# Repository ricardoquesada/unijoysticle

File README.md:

# The UniJoystiCle

The UniJoystiCle, the ultimate unicycle simulator.

It allows you to play Commodore 64 [unicycle video games](https://github.com/ricardoquesada/c64-the-uni-games) with real unicycles. Unique immersive experience, much better than VR.

This repository contains:

* the [schematic + PCB board](https://github.com/ricardoquesada/unijoysticle/tree/master/schematic) to build your own Wi-Fi receiver
* the [firmware](https://github.com/ricardoquesada/unijoysticle/tree/master/esp8266_firmware) that runs on the Wi-Fi receiver
* the [iOS client](https://github.com/ricardoquesada/unijoysticle/tree/master/client_ios) / [Android client](https://github.com/ricardoquesada/unijoysticle/tree/master/client_android) / [Desktop client](https://github.com/ricardoquesada/unijoysticle/tree/master/client_desktop): they send the packets to the Wi-Fi receiver

## Further info

* [Documentation](DOCUMENTATION.md)
* [Home page](http://retro.moe/unijoysticle)

## Videos

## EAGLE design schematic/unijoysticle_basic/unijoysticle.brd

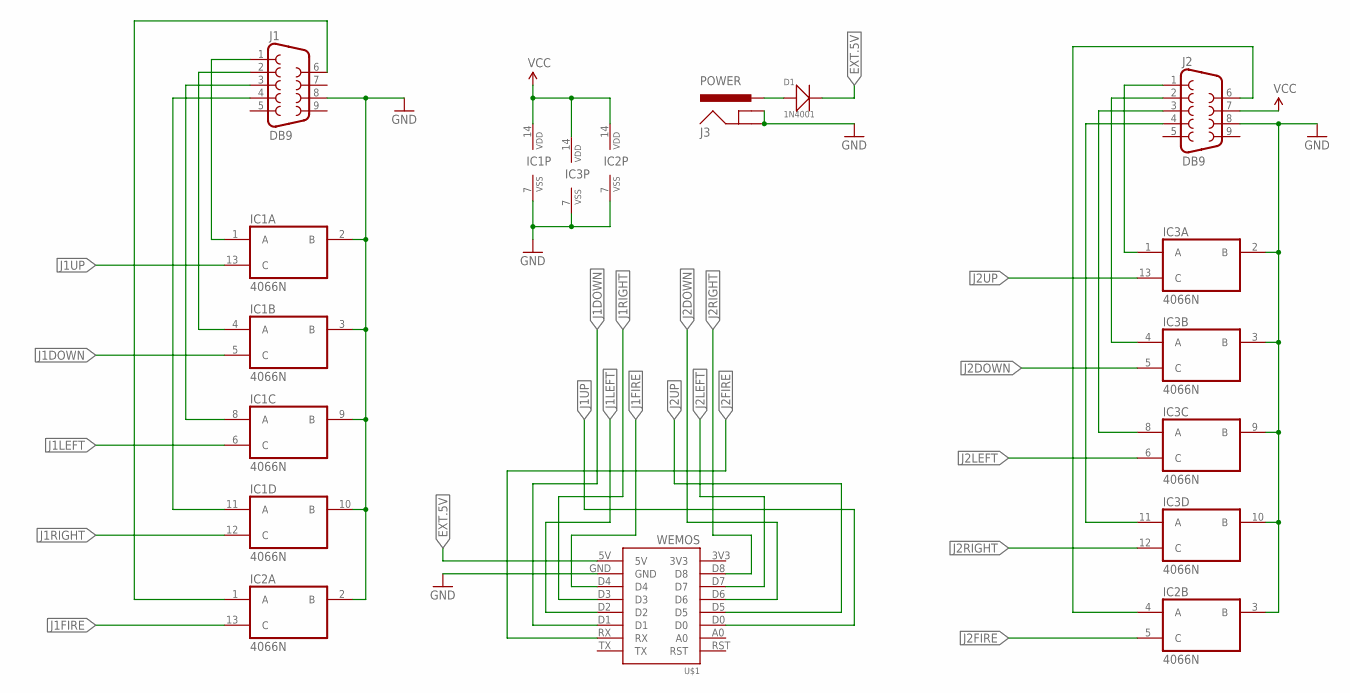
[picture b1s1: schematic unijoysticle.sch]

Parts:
D1: 1N4001; DO-41
IC1, IC2, IC3: 4066N; DIL14; MPN SN74HC4066N
J1, J2: DB9; MPN 618009231121
J3: POWER; POWER_JACK_SLOT
U$1: WEMOS

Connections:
EXT.5V: D1.2 (-), U$1.5V
GND: IC1.2 (B), IC1.3 (B), IC1.7 (VSS), IC1.9 (B), IC1.10 (B), IC2.2 (B), IC2.3 (B), IC2.7 (VSS), IC3.2 (B), IC3.3 (B), IC3.7 (VSS), IC3.9 (B), IC3.10 (B), J1.8, J2.8, J3.GND@1 (GNDBREAK), J3.GND@2 (GND), U$1.GND
J1DOWN: IC1.5 (C), U$1.D1
J1FIRE: IC2.13 (C), U$1.D4
J1LEFT: IC1.6 (C), U$1.D2
J1RIGHT: IC1.12 (C), U$1.D3
J1UP: IC1.13 (C), U$1.D0
J2DOWN: IC3.5 (C), U$1.D6
J2FIRE: IC2.5 (C), U$1.RX
J2LEFT: IC3.6 (C), U$1.D7
J2RIGHT: IC3.12 (C), U$1.D8
J2UP: IC3.13 (C), U$1.D5
unnamed: D1.1 (+), J3.PWR
unnamed: IC1.1 (A), J1.1
unnamed: IC1.4 (A), J1.2
unnamed: IC1.8 (A), J1.3
unnamed: IC1.11 (A), J1.4
unnamed: IC3.1 (A), J2.1
unnamed: IC3.4 (A), J2.2
unnamed: IC3.8 (A), J2.3
unnamed: IC3.11 (A), J2.4
unnamed: IC2.1 (A), J1.6
unnamed: IC2.4 (A), J2.6
VCC: IC1.14 (VDD), IC2.14 (VDD), IC3.14 (VDD), J2.7

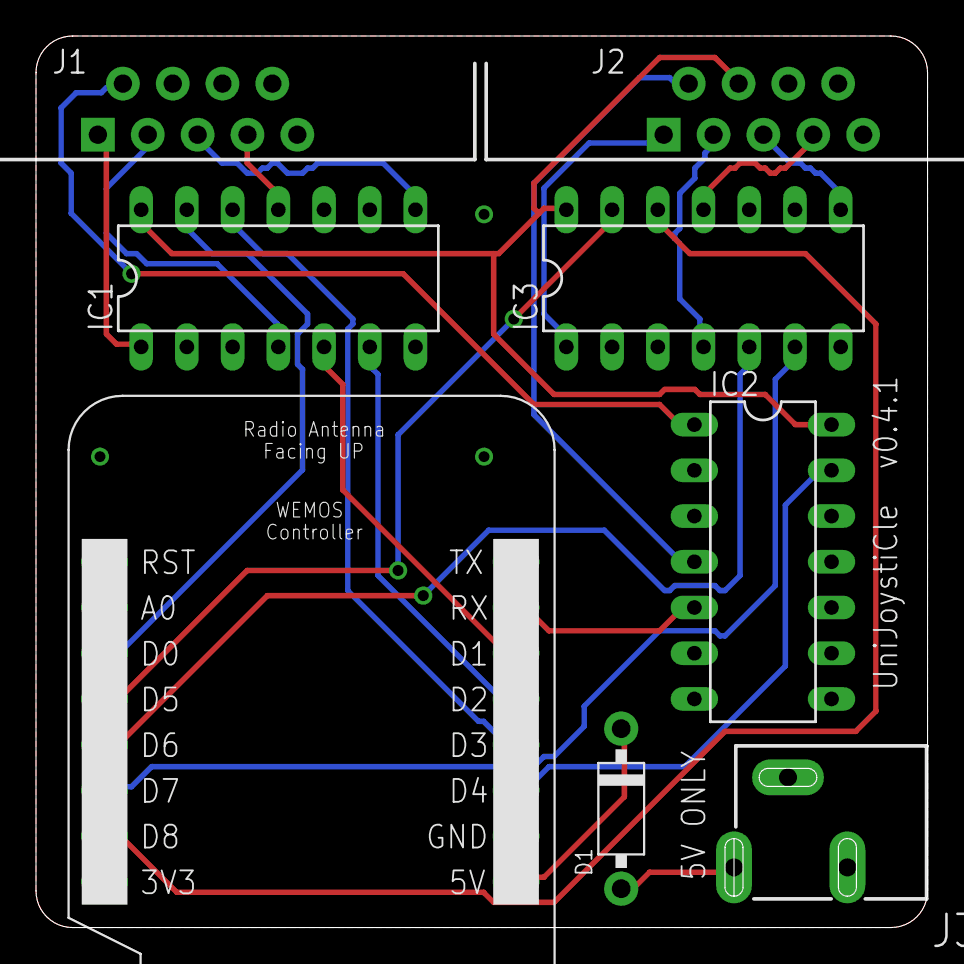
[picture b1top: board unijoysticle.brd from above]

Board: 2 copper layers, 49.5 x 49.5 mm, 8 parts (0 on the bottom side), 24 nets.

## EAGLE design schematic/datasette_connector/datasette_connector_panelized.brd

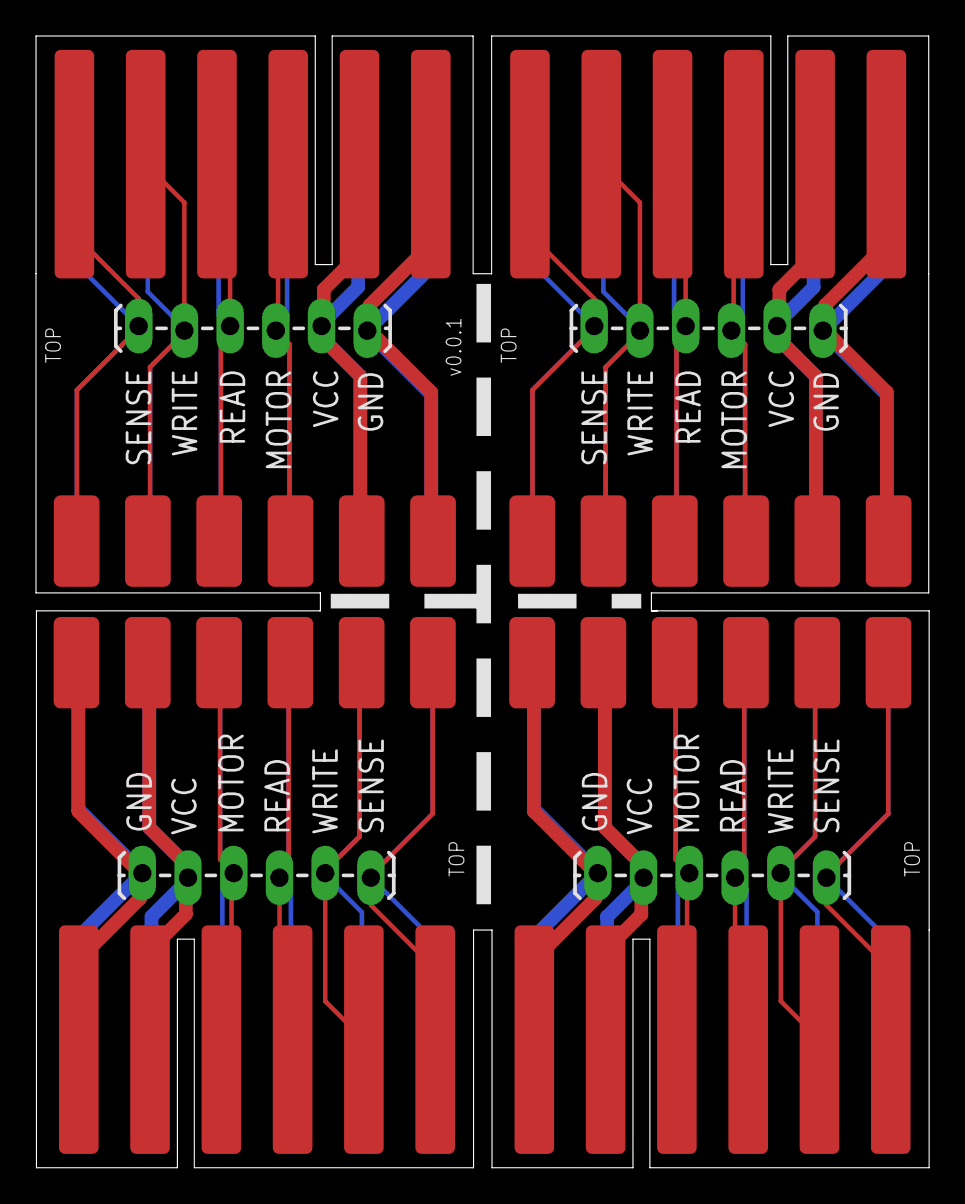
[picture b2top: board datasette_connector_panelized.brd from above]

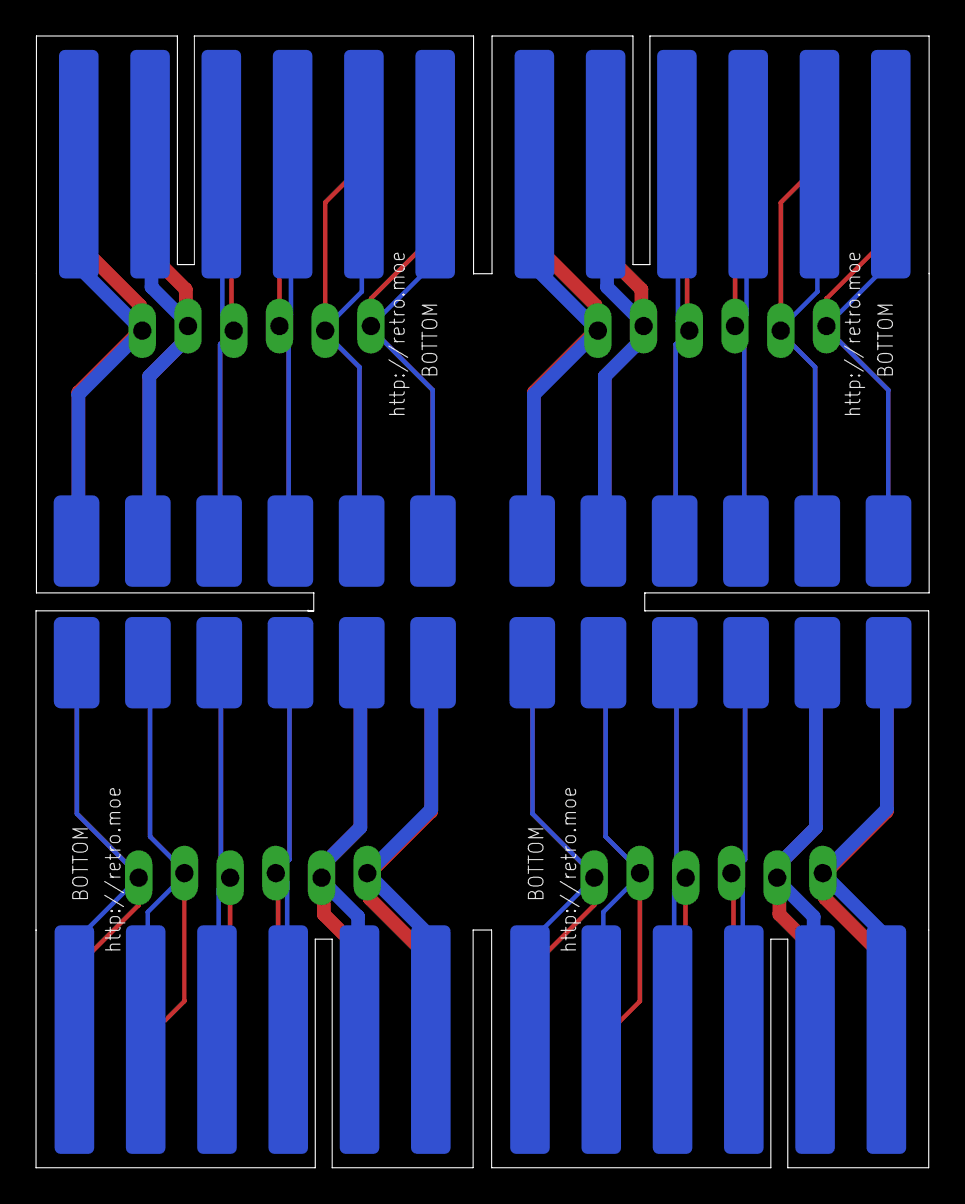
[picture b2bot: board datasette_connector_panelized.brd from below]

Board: 2 copper layers, 49.6 x 62.9 mm, 12 parts (4 on the bottom side), 24 nets.

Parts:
CN1, CN11, CN12, CN13: C64_CASETTE_EDGE; C64_CASSETTE
CN3, CN31, CN32, CN33: C64_CASETTE_CONN; C64_CASSETTE_CONN
JP, JP1, JP2, JP3: C64 CON; 1X06_LOCK_LONGPADS

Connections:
GND: CN1.1, CN1.A, CN3.1, CN3.A, JP.1
GND1: CN11.1, CN11.A, CN31.1, CN31.A, JP1.1
GND2: CN12.1, CN12.A, CN32.1, CN32.A, JP2.1
GND3: CN13.1, CN13.A, CN33.1, CN33.A, JP3.1
unnamed: CN1.5, CN1.E, CN3.5, CN3.E, JP.5
unnamed: CN1.6, CN1.F, CN3.6, CN3.F, JP.6
unnamed: CN1.3, CN1.C, CN3.3, CN3.C, JP.3
unnamed: CN11.5, CN11.E, CN31.5, CN31.E, JP1.5
unnamed: CN12.5, CN12.E, CN32.5, CN32.E, JP2.5
unnamed: CN13.5, CN13.E, CN33.5, CN33.E, JP3.5
unnamed: CN1.4, CN1.D, CN3.4, CN3.D, JP.4
unnamed: CN11.6, CN11.F, CN31.6, CN31.F, JP1.6
unnamed: CN12.6, CN12.F, CN32.6, CN32.F, JP2.6
unnamed: CN13.6, CN13.F, CN33.6, CN33.F, JP3.6
unnamed: CN11.3, CN11.C, CN31.3, CN31.C, JP1.3
unnamed: CN12.3, CN12.C, CN32.3, CN32.C, JP2.3
unnamed: CN13.3, CN13.C, CN33.3, CN33.C, JP3.3
unnamed: CN11.4, CN11.D, CN31.4, CN31.D, JP1.4
unnamed: CN12.4, CN12.D, CN32.4, CN32.D, JP2.4
unnamed: CN13.4, CN13.D, CN33.4, CN33.D, JP3.4
VCC: CN1.2, CN1.B, CN3.2, CN3.B, JP.2
VCC1: CN11.2, CN11.B, CN31.2, CN31.B, JP1.2
VCC2: CN12.2, CN12.B, CN32.2, CN32.B, JP2.2
VCC3: CN13.2, CN13.B, CN33.2, CN33.B, JP3.2

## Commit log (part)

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2016-09-02 android client: fire works as expected on dpad
2016-09-02 android client: dpad mode draws arrows WIP
2016-09-03 android client: radio dpad checked by default
2016-09-03 fix: android client. preferences are read from activites
2016-09-04 android client: server pref summary is updated onChanges
2016-09-04 android client: store images
2016-09-04 android client: resubmitted
    id is: moe.retro.unijosyticle (one unijosyticle)
    floating button: goes to documentation
    using correct title bar in actionbar
    doesn't show status bar
2016-09-04 docs: android badge size
2016-09-04 docs: android badge
2016-09-06 android client: preferences working!
2016-09-06 android client: removed unused strings
2016-09-06 android client: incorrect default for movement
2016-09-06 android client: version is 0.3
2016-09-06 docs: updates changelog
2016-09-06 docs: updates README
2016-09-07 docs: added another bug to Bugs
2016-09-08 docs: updated documentation
2016-09-08 docs: more trobleshooting info
2016-09-09 feat: Commando Mode
    Control both joysticks with one game controller
    It is called Commando Mode because you can play an unmodified
    Commando game and fire with Button A, and thorw granedes with
    Button B!!
2016-09-10 feat: Commando mode for Android
2016-09-10 fix: android client: version is 0.4
2016-09-10 fix: android client: disable radio when Commando
2016-09-10 ios client: fixes in Commando mode
    remove obsolte screenshots. using only 5.5" screenshots now
2016-09-12 docs: more info about the Commando mode
2016-09-12 docs: updated screenshots in doc
2016-09-12 docs: add game controller image
2016-09-12 docs: updated info about android controllers
2016-09-13 docs: note about WiFi Direct game controllers
2016-09-13 ios/android client: send state twice per change
    and not 60 times per second. saves battery life!
    Also fixes joystick movements in android.
2016-09-13 android client: update exclude dirs
2016-09-13 ios client: fix. remove optionals from non-optional nodes
2016-09-14 board: missing via and better labels
2016-09-14 android client: oops, dpad mode working again
2016-09-14 docs: improved doc
2016-09-14 docs: correct width/height
2016-09-14 docs: typos
2016-09-16 ios client: fix: improves iCade support
    Buttons A and D are Fire (not only A)
    Buttons B and C are Jump (not only B)
2016-09-16 ios client: verison 0.4.3
2016-09-17 android client: add analytics
    to see what is the most popular mode
2016-09-17 android client: restore SeekBarPreference
2016-09-17 android client: more cleanups
2016-09-19 client android / firmware: fixes
    client android: display error dialog if can't resolve server name
    firmware: added code for WPS support. disabled by default
2016-09-19 android client: OK instead of Ok
2016-09-19 firmware: feat: store WPS credentials in EEPROM
2016-09-20 firmware: fix: no compile-time options
    everything can be changed in runtime by setting certain values
    in the EEPROM. No possible yet to change those values, but
    will be enabled soon via TCP
2016-09-20 firmware: feat: from the webserver everything can be set
2016-09-20 firmware: better settings
2016-09-20 firmware: using C++ literals for html page
2016-09-20 docs: fixes about the barrel jack
2016-09-20 firmware: shows SSID in webpage
2016-09-20 docs: bugs are reported in the issue tracker
2016-09-21 firmware: reset joy stats + more bug fixes
2016-09-21 firmware: bette webpage
2016-09-21 firmware: redirect works ok
2016-09-22 android client: adds missing text strings for in18
2016-09-22 android client: resolves unijoysticle.local + unijosyticle mode
    unijoysticle mode:
    - correct rotation: uses x instead of y
    - z > threshold instead of z < -threshold
2016-09-22 docs: changelog
2016-09-22 android client: report error if cannot resolve server address
2016-09-22 android client: analyzer fixes
2016-09-22 android client: NSD major fix
    resolves correctly. does not try to send another rquest
    is one is still in progress
2016-09-23 ios client: migrated to Xcode 8 + swift 2.3
2016-09-23 ios client: adds Stats & SEttings for WiFi device
2016-09-23 android client: Server -> WiFi device
2016-09-23 ios controller: shows version in settings
    and other minor fixes
2016-09-23 docs: documentation improved
2016-09-23 docs: adds TM
2016-09-24 android client: correct name
2016-09-24 firmware: test for web update
2016-09-24 Create gh-pages branch via GitHub
2016-09-24 docs: test
2016-09-24 firmware
2016-09-24 firmware latest version
2016-09-24 firmware: upgrade firmware works
2016-09-24 new firmware
2016-09-24 firmware: fetch firmware from correct localtion
2016-09-24 firmware: correct URL for upgrade
2016-09-24 latest firmware
2016-09-24 more info
2016-09-24 docs: info about install firmware
2016-09-25 firmware v0.4.3
2016-09-25 icons
2016-09-25 fixes in icons
2016-09-25 docs: more info about flashing the nodemcu
2016-09-25 docs: more on flashing firmware
2016-09-30 ios client: remove ?)! ... just a ! is enough
2016-10-03 docs: better power consumtion
2016-10-07 schematic: adds diode again
    I don't know if it is really needed, but it is scary
    to see the c64 LED on, even if the computer is off
    when the unijosyticle is being powered by USB,
    but externally connected to the datassette port
2016-10-07 board: adds 3 vias
2016-10-07 board: label "unijoysticle" better position
2016-10-07 board: longer pads for wemos
2016-10-14 desktop client: displays the arrows
    still WIP
2016-10-14 desktop client. getting better
2016-10-14 deskop client: adding icons and other stuff
2016-10-16 desktop client: utils and other files
2016-10-18 desktop client: resolves mdns
    and sends joystate
2016-10-18 desktop client: adds quit
2016-10-19 desktop client: better handling the creation...
    ...of Main Window
2016-10-19 desktop client: linear mode fixes
    no more settings. added possibility to change both
    joysticks with two different sliders
2016-10-19 desktop client: adds preferences
2016-10-19 desktop client: better internal design...
    ... in settings.
    settings are monolithic now. easier. don't need the super-dooper
    modular design
2016-10-20 desktop client: command mode works
    ...but no gamepad support yet
2016-10-25 desktop client: initial gamepad support
2016-10-28 Linear -> Commodore Home
2016-10-29 android client: clear event after 160ms in Home mode
2016-10-30 android client: home fixes
    alarm switch works
    fix play/stop buttons
2016-11-04 ios client: Commodore Home almost there
2016-11-04 ios client: migrated to Swift v3.0
2016-11-05 desktop client: commodore home
2016-11-07 desktop client: works with dpads. all modes
2016-11-07 desktop client: fixes crashes
2016-11-07 docs: changelog update for buttons X and Y in Commando mode
2016-11-07 firmware: allows changing the MDNS name
    v0.4.4
2016-11-07 firmware: Name, not name
2016-11-07 desktoip client: better defaults for mdi widget
2016-11-07 desktoip client: correct name for mac
2016-11-07 latest firmware is v0.4.4
2016-11-07 adds windows app
2016-11-07 downloads links
2016-11-07 better homepage
2016-11-08 display version correctly
2016-11-08 binary for Mac is v0.4.0
2016-11-08 no longer beta
2016-11-08 spaces in name
2016-11-08 documentation updates
2016-11-08 firmare v0.4.5
2016-11-08 firmware: remove reset
2016-11-08 docs: screenshots for documentation
2016-11-08 docs: new screnshot with commodore home
2016-11-08 docs: changelog fixes
2016-11-11 schematic: datasette port bottom names fix
2016-11-12 board: datasette: adds panelized version
2016-11-14 laytout: datasette connect panelized fixes
    gap has 1mm instead of 0.6mm since Seeed Studio doesn't support it
2016-11-14 v0.4.1 for macOS
2016-11-14 v04.1. for windows client
2016-11-15 client desktop: win32 fixes in location .exe
2016-11-15 adds v0.4.2. windows
2016-11-18 android client: updates project to use latests sdks
2016-11-27 v0.4.2a
2016-11-27 v0.4.2a for desktoip client mac
    includes plugin
2016-11-28 updates readme
2016-11-28 adds controllers videos
2016-12-12 android: using new gradle plugin
2016-12-15 script to panelize it
2016-12-15 binary vice 3.0
2016-12-28 android client: works on API level 16 (Android v4.1)
2016-12-29 docs: adds firmware docs
2016-12-29 docs: cosmetic
2017-01-04 esp32: kind of works pot + udp server
2017-01-04 esp32: more reliable
2017-01-05 docs: readd gitter
2017-01-06 using built-in microseconds delay
2017-01-06 firmware esp32: doing more experiments
    still NEGEDGE doesn't work as expected.
    Not sure whether the bug is in my code or in the IDF
2017-01-08 esp32: more trial and error
2017-01-17 reorganized schematic directory
2017-01-22 desktop: Commodore Home sends only joy #2
2017-01-23 esp32: updated to esp-idf v2.0-rc
2017-01-23 android: version 0.4.13
2017-01-23 testpot bas from r.carlsen
2017-01-24 c64 test: pot + joy works
2017-01-26 works! one pot only
2017-01-27 missing files
2017-01-27 android client: unijosyticle mode better defaults
    movement threshold default value fixed
2017-06-18 WIP: digi-pot driver for esp32 based unijoysticle
2019-01-06 v2: PoC. add hid-gamepad
    move old esp32 to old folder
2019-01-06 add localhost test.
    easier to test everything in localhost and in esp32.
    once ready, should be flashed to esp32
2019-01-07 tool: parsing for asus... works
2019-01-07 template to compile sdk for esp32 + btstack
2019-01-07 firmware esp32: turns on a led
2019-01-08 esp32: new asus device
2019-01-09 esp32: accept connections
2019-01-10 esp32: add vscode properties
2019-01-10 esp32: more cases for switch
2019-01-11 esp32: printf typo
2019-01-14 ios: compiles, but crashes with thread concurrent bug
    this is a new features in swift 4
2019-01-14 esp8266: wps disabled by default
    since newer firmwares come with it disabled
2019-01-17 esp32: asus gampead by default in test
2019-01-17 esp32: discovery and reconnect altogether
2019-01-19 reconnect works!
2019-01-19 esp32: shuffling code...
    cleaning up code... adding gap query
2019-01-19 esp32: auto-connect from discovery...
    ...sometimes it works
2019-01-19 esp32: should not disconnect on "incomming connection"
2019-01-20 esp32: incoming works as expected
2019-01-20 esp32: moving sdp to device struct
2019-01-20 esp32: descriptor len fixes. 16-bits now instead of 8
2019-01-20 esp32: better names
2019-01-21 esp32: error check
2019-01-21 esp32: multi-controller works ok
2019-01-21 esp32: spaghetti code, bug multiple connection/reconnection/discoveries works
2019-01-21 esp32: more info in README
2019-01-22 esp32: more debug info
2019-01-22 esp32: almost getting rid of current_device
2019-01-22 esp32: copy firmware to esp32...
    works on the ESP32 as well on the PC
2019-01-22 esp32: updated doc
2019-01-22 esp32: clean up code a bit
2019-01-23 esp32: fix some connection / reconnection issues on certain devices
2019-01-25 esp32: recognizes mouses and tries to connect to them
2019-01-27 esp32: "correctly" parses hat and x,y,z...
2019-01-27 esp32: remove LED. they are output only
2019-01-28 esp32: joy report almost ready
2019-01-28 esp32: indents + assign joy port
2019-01-29 esp32: kind of working with gpios
2019-01-29 esp32: almost there... ?
2019-01-29 esp32: joystick works!
2019-01-30 Vagrant files
2019-01-30 esp32: sdkconfig
    use 80Mhz by default.
    UART0 GPIO1 and GPIO3 (which are the default)... tryied using
    different ones, but as expected, no output.
    I need GPIO3 free... we'll see
2019-01-30 esp32: usin GPIO 27 for fire B
2019-01-31 esp32: another mini refactor...
    moved parsing stuff to "hid_parser"
2019-01-31 esp32: button "b" is "jump"... triggers up movement
2019-01-31 esp32: on_gap event is a function
2019-02-01 esp32: cleaner fixes
2019-02-02 esp32: cleaning code... still too much code to clean
2019-02-02 esp32: minor fixes plus using esp-idf v3.1.2 instead of master
2019-02-02 esp32: honor with BlueKitchen license
2019-02-02 esp32: missing ; oops
2019-02-03 esp32: using common files from esp32 build
2019-02-03 esp32: by default, VERBOSE_LOGGING until we are production ready
2019-02-04 esp32: assign joystick port works
2019-02-04 esp32: initial mouse support
2019-02-04 esp32: mouse WIP
2019-02-05 esp32: mouse working... sort of... needs improvements
2019-02-06 esp32: more resolution for axis
    and other mouse fixes

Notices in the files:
parts and their libraries:
SparkFun: Licensing: CC v3.0 Share-Alike You are welcome to use this library for commercial purposes.
SparkFun-Aesthetics: Licensing: Creative Commons ShareAlike 4.0 International - https://creativecommons.org/licenses/by-sa/4.0
